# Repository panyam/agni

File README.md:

# Agni

Agni checks schematics and boards for design mistakes, such as an I2C bus with no pull-up, a power
rail with no decoupling, a USB connector with no ESD protection, or a track narrower than the
board's own rules. It reads KiCad, OrCAD Capture, EDIF, xschem and gEDA schematics, and KiCad,
Allegro, Altium, ODB++ and IPC-2581 boards. Every finding names the net or part it fired on and
locates it on the schematic.

**[Open the demo in your browser](https://panyam.github.io/agni/demo/)** and drop a KiCad or EDIF
design on the page, or open one of the example boards. The engine runs in the page as WebAssembly,
so your design is never uploaded.

## Watch a walkthrough

A 33-second walkthrough on Antmicro's open-source Jetson AGX Thor baseboard. It finds a resistor by
name, and the schematic and the board beside it both go to it. Then a click on a test point on the
board takes the schematic to that point's page. `make demo-video JOURNEY=find-a-part` records it.

https://github.com/user-attachments/assets/b399f9d5-5440-4de5-8c01-5e1742dbefdf

A 92-second walkthrough of what changed between two revisions of the same board, Antmicro's rev
1.1.0 and rev 1.1.3. It steps through one change of each kind, an added, a removed and a changed
part, a new, a deleted and a renamed net, and a net whose connections changed, and each step says
what that kind means. `make demo-video JOURNEY=compare-revisions` records it.

https://github.com/user-attachments/assets/1ff74453-c8a3-4b29-8727-99e301f905f8

A 43-second walkthrough that follows a signal outwards from a part on the same board. It starts at
R361, a pull-up on the I2C connector's data line, and walks one hop through small parts, where it
stops at the 3.3 V rail. One hop wider it crosses the level shifter U80 to the module's 1.8 V side,
and then it asks for the route to the rail. `make demo-video JOURNEY=walk-a-signal` records it.

https://github.com/user-attachments/assets/eb9f4803-4316-4d4b-8de4-8aa52e9484a0

## What does it do

- **Runs ERC/DRC-like structural checks.** They catch missing I2C pull-ups, unprotected
  exposed signals, power rails without decoupling, and boards that fail track-width rules. Findings come out in
  plain language and cite the net or component they fire on.
- **Runs a browser viewer.** `agni open <design>` serves one board and prints its URL; `agni serve` opens a
  tree of them. Either renders the design, runs the checks, and locates each finding on the canvas.
- **Runs in the browser with nothing installed.** The engine also compiles to WebAssembly, so the
  [public demo](https://panyam.github.io/agni/demo/) opens a KiCad or EDIF design you drop on the
  page, checks it, queries it and saves a report, without sending the design anywhere.
- **Walks a review checklist and traces signals.** `agni review` scores a design against a team's
  checklist and saves the page, and `agni trace --from U7.3 --to U12.4` follows a signal through
  the series parts between two pins.
- **Checks against datasheets.** It joins a design against extracted datasheet limits and
  checks, for example, that a rail is inside a part's recommended operating range.
- **Diffs revisions over the IR.** It compares two revisions structurally (components, nets,
  connectivity), not as a text diff of the source files, so it survives reformatting and
  rename churn.
- **Renders to SVG or a WebGL canvas**, drawing either the faithful schematic and board
  geometry or an auto-laid-out netlist graph.
- **Answers datalog queries.** `agni query` asks arbitrary questions of the design fact base.
  The rules are built on the same fact base, and the engine is
  [jaala](https://github.com/panyam/jaala).
- **Reads many formats into one IR.** EDIF netlists and schematics, KiCad schematics and
  boards, IPC-2581, xschem, and gEDA all parse into the same `ir.Design`. Adding a reader is
  one entry in `readers/formats/registry.go`.
- **Serves the same answers to other tools.** The CLI calls a set of services, and `agni serve`
  exposes the same services as Connect rpcs. `--remote` sends `query`, `check`, `trace` and `review`
  to a running server, and [`clients/python`](clients/python) is a typed Python client over the CLI
  or a server.

## Try it in 60 seconds

With nothing installed, the [public demo](https://panyam.github.io/agni/demo/) checks a seed
board or a file you drop on it, in your browser.

To run the CLI, install it one of three ways:

```
go install github.com/panyam/agni/cmd/agni@latest
```

or download the tarball for your platform from the
[latest release](https://github.com/panyam/agni/releases/latest) and put `agni` on your PATH, or
run the container image with no install at all:

```
docker run --rm -v "$PWD":/work -w /work ghcr.io/panyam/agni check <board>.kicad_sch
```

Then check the demo board, which has deliberate design issues:

```
curl -sLO https://raw.githubusercontent.com/panyam/agni/main/demo/showcase.fires.kicad_pro
curl -sLO https://raw.githubusercontent.com/panyam/agni/main/demo/showcase.fires.kicad_sch
agni check showcase.fires.kicad_pro
```

```
findings by rule:
  bulk-cap               2
  decoupling-present     2
  esd-protection         2
  i2c-pull-up            1
  input-protection       1
  reverse-blocking-absent 1
  test-point-coverage    2

first 11:
  [warning] bulk-cap: +3V3 (power rail has no bulk capacitor)
  ...
  [error] i2c-pull-up: /SCL (I2C net has no pull-up resistor to a rail)
  [warning] input-protection: VBUS (connector feeds a power input with no fuse or TVS in the path)
  ...
```

`agni open showcase.fires.kicad_sch` serves the board in the browser viewer and prints its URL. Press
Run checks and click a finding to locate its net on the schematic. A release binary carries the
viewer, and a `go install` build downloads it from its release the first time it needs it.

From a checkout, `make agni` builds the same binary into `bin/`, and `make demo` opens both demo
boards, the clean one and the one with issues. See [demo/README.md](demo/README.md).

Each [GitHub release](https://github.com/panyam/agni/releases) attaches a compose bundle pinned to
it. The bundle runs the `ghcr.io/panyam/agni` image over your own boards:

```
AGNI_DESIGNS=./designs docker compose up -d     # the viewer at http://localhost:8080
docker compose run --rm trial /designs/<board>  # a trial report that holds nothing from the board
```

## How it works

Agni normalizes design formats the way a compiler normalizes languages into one AST, so every
analysis downstream is written once and works on all of them. The protobuf IR is the one contract
in the middle. It is defined in `protos/` and generated into `gen/`. Readers are the only code that
knows a file format, and they produce `ir.Design`. They are `readers/edif/`, `readers/kicad/`,
`readers/ipc2581/`, and the xschem/gEDA readers. Everything else consumes the IR and never looks
at a source file. That includes `core/check/`, `core/diff/`, `core/render/`, the query engine and
the web service.

The same shape repeats at two more contracts. N producers fill a geometry IR and N renderers draw
it. N datasheet extractors fill a parameter IR and the checks read it.

## Philosophy

- **One neutral IR serves every format.** A schematic is a schematic whether it came from KiCad,
  EDIF, or IPC-2581. Normalize each format once, and write every analysis once against the
  IR. Add a reader and every check, diff, render, and query works on the new format; add an
  analysis and it works on every format.
- **Format-neutrality is enforced in CI.** Analyses read the IR, never source
  files, and the IR carries no field a second format could not populate. Architectural
  constraints checked in CI keep the core from accreting format-specific special cases.
- **Silence is never coverage.** A check that cannot evaluate reports "not applicable" or
  flags what it could not model; it never returns a false pass. Findings cite the net,
  component, or datasheet page they come from, and unverified data is marked as such. You can
  always tell "clean" from "not checked".
- **Verify against reality.** Readers and rules are checked against the native tools
  (`kicad-cli` ERC/DRC) and real design exports, not only hand-written fixtures. A feature is
  done when it works on a real file.
- **The core is open, with a clear boundary.** The engine is shareable under Apache-2.0.
  Proprietary formats, house rules, and confidential designs live in a private extension that
  depends on the engine without forking it.
- **Agni is written to be legible to software engineers.** EDA carries decades of domain
  vocabulary. Agni maps that vocabulary to concepts software engineers already know (an IR, a
  linter, a semantic diff, a lockfile), so you can contribute without an EE degree. See
  [the software-analogy map](https://panyam.github.io/agni/reference/analogy/).

## Formats read today

| Format | Extensions | Netlist | Faithful geometry |
| --- | --- | --- | --- |
| EDIF 2.0.0 | `.edn` `.edf` `.edif` (netlist), `.eds` (schematic) | yes | schematic |
| KiCad | `.kicad_sch` `.kicad_pcb` `.kicad_pro` | yes | schematic + board |
| IPC-2581 | `.xml` `.cvg` | yes | board |
| xschem | `.sch` (sniffed) | yes | schematic |
| gEDA gschem and Lepton | `.sch` (sniffed) | yes | schematic |
| Telesis | `.tel` | yes | none |
| OrCAD Capture | `.dsn` | yes | schematic |
| Cadence Allegro | `.brd`, from Allegro 16.6 and 17.2 | yes | board |
| Altium Designer | `.PcbDoc` | yes | board |
| ODB++ | a job directory, `.tgz`, `.zip` | yes | board |

A hierarchical EDIF netlist reads its top cell by default and says which blocks it left out. To
read every block it places, pass `--flatten-hierarchy`, set `flatten_hierarchy: true` in the
design's `design.yaml`, or press **Read every block** in the viewer.

## Documentation

Full documentation lives at [panyam.github.io/agni](https://panyam.github.io/agni/).

- [Getting started](https://panyam.github.io/agni/guide/getting-started/) covers installing,
  a first check, reading the report, and gating CI.
- [User guide](https://panyam.github.io/agni/guide/) covers concepts, the CLI, checks, diff, and
  the query language, for someone new to the tool.
- [Software-analogy map](https://panyam.github.io/agni/reference/analogy/) maps
  hardware ideas onto software ones. If you read code but not schematics, start here.
- [Overview](https://panyam.github.io/agni/overview/) opens the engineering docs on IR and
  ingestion, geometry and rendering, semantic diff, and the format primers.
- [examples/README.md](examples/README.md) lists runnable walkthroughs, one per feature.
- [CONSTRAINTS.md](CONSTRAINTS.md) holds the enforceable architectural rules. Read it before
  proposing changes.
- [SECURITY.md](SECURITY.md) says how to report a vulnerability.
- [Open core](https://panyam.github.io/agni/decisions/open-core/) explains the split between this
  public engine and a private extension that adds proprietary readers and rules without forking
  it.

## Status

Agni reads real exports from every listed format and runs its full analysis over them. It is
young, with bounded format coverage (see each reader's notes), a growing rule catalog, and an
early datasheet extraction pipeline. The architecture is settled and the breadth is still
growing. Issues and readers for new formats are welcome.

## Building

`make build` requires Go 1.26.9 and pnpm (for the web viewer bundle). `make testall` also needs
`buf` 1.61 on your PATH, `python3`, a Chromium for the browser tests, and network access to fetch
the pinned sample corpus. `CONTRIBUTING.md` has the details.

```
pnpm install                      # once: the web workspace (web/, web-shared/, datasheet/web/)
make build                        # web bundle + go build ./...
make install                      # install the agni CLI to $GOBIN
make testall                      # the full gate: vet, lint, gosec, gitleaks, Go, wasm, web, browser and Python tests, docs checks
```

## License

Apache-2.0. See [LICENSE](LICENSE) and [NOTICE](NOTICE).

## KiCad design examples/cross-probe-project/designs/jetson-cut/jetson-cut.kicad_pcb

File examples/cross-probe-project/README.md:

# Cross-probe walk project

`make exercise-cross-probe` walks the cross-probe mission (agni issue 1321) on a board: open the
schematic and the board as two linked views, click a part in one and find it in the other, turn the
board over. The gate walks this project, and the mission's real-board run walks the whole Jetson board in
`examples/jetson-project`.

Mission #1586 grows the same walk. Its first steps turn the board view away from C133, a back-side
capacitor, then click C133 on the schematic. The board view turns over to its back on its own and
shows B.Cu (agni issue 1587). A later step hides In5.Cu and clicks `Net-(Q2-G)` on the Power sheet.
That net runs on In5.Cu, so the board view turns In5.Cu back on. With the board view's Follow side
box cleared, the same clicks change neither. Then Back steps to C133 and Forward to `Net-(Q2-G)` again
(agni issue 1588). Last, a click on GND puts "1 of 2" in the canvas bar, and the next-sheet control
opens the other sheet that draws GND, lit and centred (agni issue 1589). To see it by hand, run `agni
open examples/cross-probe-project/designs/jetson-cut` from the repo root, open the Board tile beside
the canvas, and click C133. Press `[` and `]` to step through what you clicked, and `,` and `.` to
step through the sheets.

`designs/jetson-cut` is a cut of the Antmicro baseboard for Jetson AGX Thor, Copyright (c)
2025-2026 Antmicro, licensed under the Apache License, Version 2.0. `make cut` regenerates it from
the fetched samples corpus with `tools/kicadcut`. It keeps two sheets and the board's copper around
the parts on them, so it stays small enough to commit.

| Sheet | Part | Board side | Angle on the board |
| --- | --- | --- | --- |
| USB Debug, PD | C133, C134 | back | 0 |
| USB Debug, PD | C135 | back | 90 |
| USB Debug, PD | C44 | back | -90 |
| USB Debug, PD | R119, R120, D20, D21 | front | 180 |
| USB Debug, PD | R123, R124 | front | 0 |
| Power | Q5, U61, U6 | back | 90 |
| Power | C261, C34 | back | 0 |
| Power | C30, C38 | back | 180 |
| Power | TP76 | front | 0 |
| Power | Q2 | front | 90 |

The board keeps those nineteen footprints, the 397 track segments and 202 vias on their nets inside
4 mm of them, and the board outline. It drops the copper pours, which reach across the whole board,
and the footprint artwork on the User layers, which agni does not draw.

A cut ends some of the design's nets, and the cut schematic names those for itself, so `make cut`
renames each board net to the name kicad-cli's netlist of the cut gives its pads, as KiCad's Update
PCB from Schematic would. agni reads every part pin onto the net kicad-cli's netlist names, and
every pad onto its pin's net. `TestTheCrossProbeCutJoinsItsSchematicToItsBoard` holds the second.

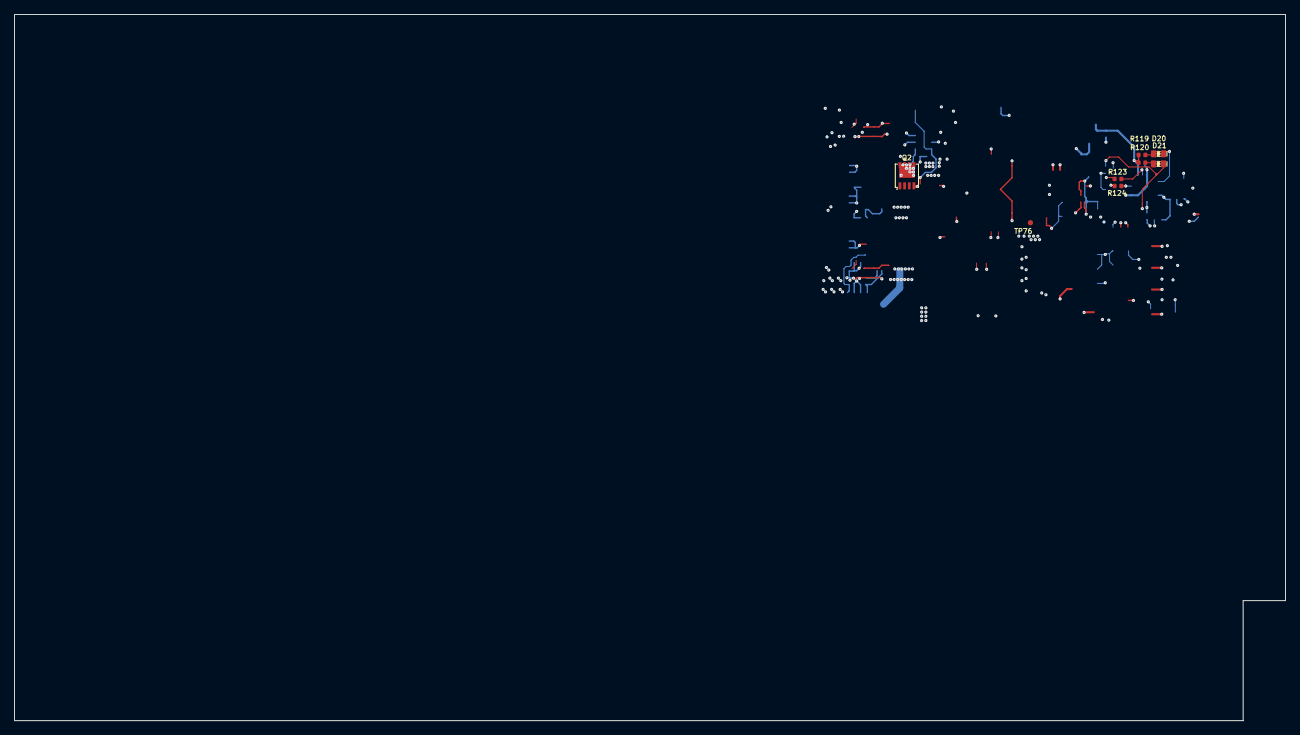
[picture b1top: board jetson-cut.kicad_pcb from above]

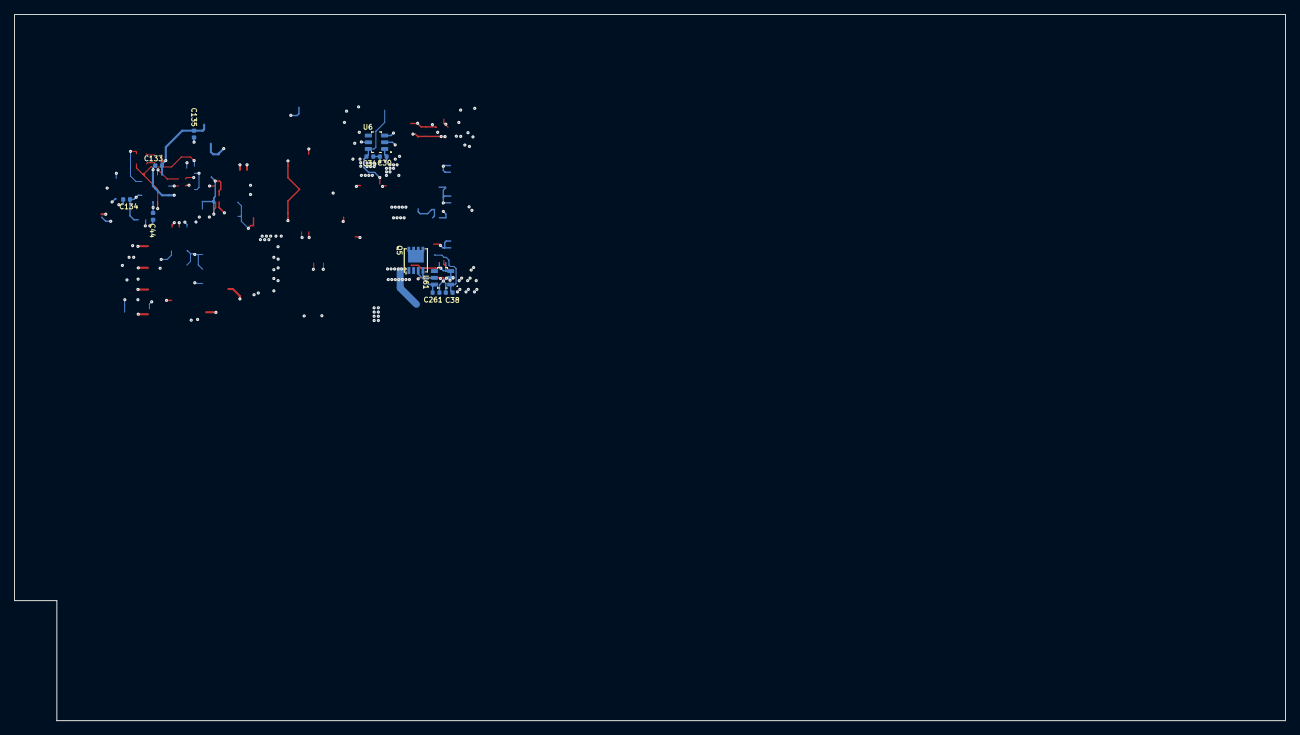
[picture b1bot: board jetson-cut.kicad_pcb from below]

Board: 10 copper layers, 180.0 x 100.0 mm, 19 parts (11 on the bottom side), 9 nets.

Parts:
C30, C38, C44, C133, C134: C_100n_0402; C_0402_1005Metric
C34, C261: C_1u_25V_0402; C_0402_1005Metric
C135: C_10u_0402; C_0402_1005Metric
D20, D21: LED_G_0603_LTST-C190GKT; LED_0603_1608Metric_G
Q2, Q5: SISS05DN-T1-GE3; Vishay_PowerPAK_1212-8_Single
R119, R120: R_200R_0402; R_0402_1005Metric
R123, R124: R_0R_0402; R_0402_1005Metric
TP76: TP_0.75mm_SMD; TP_SMD_0.75mm
U6, U61: LTC4412IS6; SOT-23-6

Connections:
/Power/USBPD1_HV: C38.2, Q5.5 (D), TP76.1, U61.1 (IN)
/USB Debug, PD/FTDI_3V3: C44.1, C133.1, C134.1, C135.2, R119.2, R120.2
GND: C30.1, C34.1, C38.1, C44.2, C133.2, C134.2, C135.1, C261.1, U6.2 (GND), U6.3 (CTL), U61.2 (GND), U61.3 (CTL)
unnamed: D20.2 (A), R119.1
unnamed: D21.2 (A), R120.1
unnamed: C30.2, Q2.5 (D), U6.1 (IN)
unnamed: Q2.4 (G), U6.5 (GATE)
unnamed: Q5.4 (G), U61.5 (GATE)
unnamed: C34.2, C261.2, Q2.1 (S), Q2.2 (S), Q2.3 (S), Q5.1 (S), Q5.2 (S), Q5.3 (S), U6.6 (SENSE), U61.6 (SENSE)

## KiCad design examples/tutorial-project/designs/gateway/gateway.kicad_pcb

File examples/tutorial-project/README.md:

# Tutorial project

The worked example the tutorial track is built on: one synthetic board and the project files a team
wraps around it. Every part, MPN, vendor, and datasheet value here is invented, so the whole folder
is redistributable and nothing on it is anyone's real design.

## Try it

```
make review
```

That runs the `review` checklist in `project.yaml` over the bundled board with every tier this
project supplies, and prints one outcome per item. `make help` lists the rest.

Note what the command does **not** carry: no `--conventions`, no `--profile-path`, no `--params`, no
`--intent-path`. The board resolves to this project, and the project's config is read from
`project.yaml` and from beside it. That is also what keeps it from reaching anywhere else. A design in another project,
or in none, cannot be checked against these rules, because config travels along the design-to-project
edge rather than along the command line.

## Layout

This is the shape a real review project takes. Two kinds of file live here.

**Per-project**, shared by every design:

| Path | What it is |
|---|---|
| `project.yaml` | the project's name, which is what makes this folder a project rather than a folder |
| `project.yaml` `conventions:` | house naming, which says which net names are rails and what a legal name looks like |
| `project.yaml` `checklists.review` | the checklist of questions this team asks of every board, and the project's default since it is written first |
| `project.yaml` `checklists.house` | a second checklist whose inline query calls this project's own library in `lib/`, run with `--checklist house` |
| `profiles/` | interface declarations, one per bus this team designs with |
| `params/` | datasheet parameter sets, one per part worth checking against its limits |
| `lib/` | this team's own derived relations, one Datalog module per `.dl` file, such as `house.pmic_rail` |
| `reports/<design>/` | the outcome of a run on one design, written by `make report` |

**Per-design**, one set per folder under `designs/`:

| Path | What it is |
|---|---|
| `design.yaml` | the design's name, which file is its entry, and which files are views of it |
| `gateway.edn` | the netlist, `gateway-rev-b.edn` a later revision of it, and `gateway-rev-c.edn` one more that renames and rewires a net, for `diff --rename-approx` |
| `gateway.kicad_sch` | the same board as a KiCad schematic, with `symbols/` as an external library |
| `gateway.kicad_pcb` | the same board's copper, for the board-tier checks |
| `design.yaml` `intent:` | what this board is supposed to be: declared modules and what each rail is |

Intent is per-design because each board has its own intended architecture. Conventions, profiles,
and parameters are per-project because they describe the team, not the board.

The two descriptors are what let you name a **design** instead of a file. `agni check
designs/gateway` reads the entry `design.yaml` declares and picks up the board companion for the
copper checks, so the connectivity rules and the board rules run from one argument. Naming a
declared companion (`agni check designs/gateway/gateway.kicad_pcb`) reads the entry instead and says
so on stderr, because a board export is a view of the design rather than a second source of it. Pass
`--as-named` when reading a view as a netlist is the point, which is what `make check-views` does.

## What the board is built to show

The board is deliberately imperfect. Each flaw exists so some part of the tool has something true
to report rather than a contrived one.

- **Rails are named function-first** (`PMIC_CORE_3V3`), which the built-in rail vocabulary does not
  match. Without the `conventions:` section the only rail on the board is `GND`. That is what the
  lexicon half of a conventions section is for, and running `agni check` with and without it shows
  the difference.
- **CAN is present, complete, and terminated, but has no ESD part on the pair.** So the built-in
  CAN profile has exactly one real finding. `profiles/can.yaml` then supersedes that built-in and
  adds a standby signal this project always routes, which the board does not, so a second finding
  appears when the overlay profile loads.
- **LIN is absent entirely.** Its checklist item must not score a pass just because a check for a
  bus that is not there found nothing to complain about.
- **U2's datasheet parameters are a mock placeholder**, not a transcription. Its finding reports as
  `provisional` rather than `fail`, which is the engine declining to call a defect on data nobody
  has checked. `params/acme-buck-3v3.textproto` is the seeded-and-trusted contrast.
- **One intent declaration is deliberately wrong.** The core domain is declared at 3.3 V while its
  rail is an actual 1.8 V rail, so the intent check has a real deviation to find.
- **The entry file is a netlist, which carries no copper.** The board-tier item is answered from
  the `.kicad_pcb` that `design.yaml` declares as a companion. A design declaring no board reads
  `n/a` there, which means the question does not apply to what was loaded, and that is not a pass.

## A note on the netlist

One rule about the EDIF decides whether pins connect at all, and it is easy to get wrong when
writing one by hand.

A `portRef` names a port by its **designator**, not by the port's name. Use the name and the
connection never joins to the pin, so pin-level rules see an unconnected part while `stats` looks
perfectly healthy.

Each part cell here also declares its own `(designator "<prefix>")`, which is how a cell states the
reference-designator prefix its instances use. That is good practice rather than a requirement,
since a cell that omits it falls back to the prefix on each instance's own ref-des. It used to be
required here for a different reason, because the reader would take a *port's* designator when a cell
declared none, and every component of that cell then classified as unknown. That was agni issue 109
and it is fixed.

## What this fixture is, and how its views stay in step

`examples/tutorial-project/` is the shareable review-project fixture the docsite tutorial runs on, a
synthetic sample board in three views (`.edn` plus a rev-b, a `.kicad_sch` with an external symbol
library, a `.kicad_pcb`) with a `project.yaml` carrying its conventions and checklists,
`profiles/`, `params/`, and a
`design.yaml` per design carrying its `intent:` section. The KiCad views are GENERATED from the netlist by `tools/`. From
inside `examples/tutorial-project/`, `make check-views` fails if the three stop describing the same
design, and `make regen-views` rebuilds them after any netlist edit (both targets live in this
folder's own Makefile, not the root one). It is not a Go module, so `make testall`'s
`examples/*/go.mod` glob skips it.

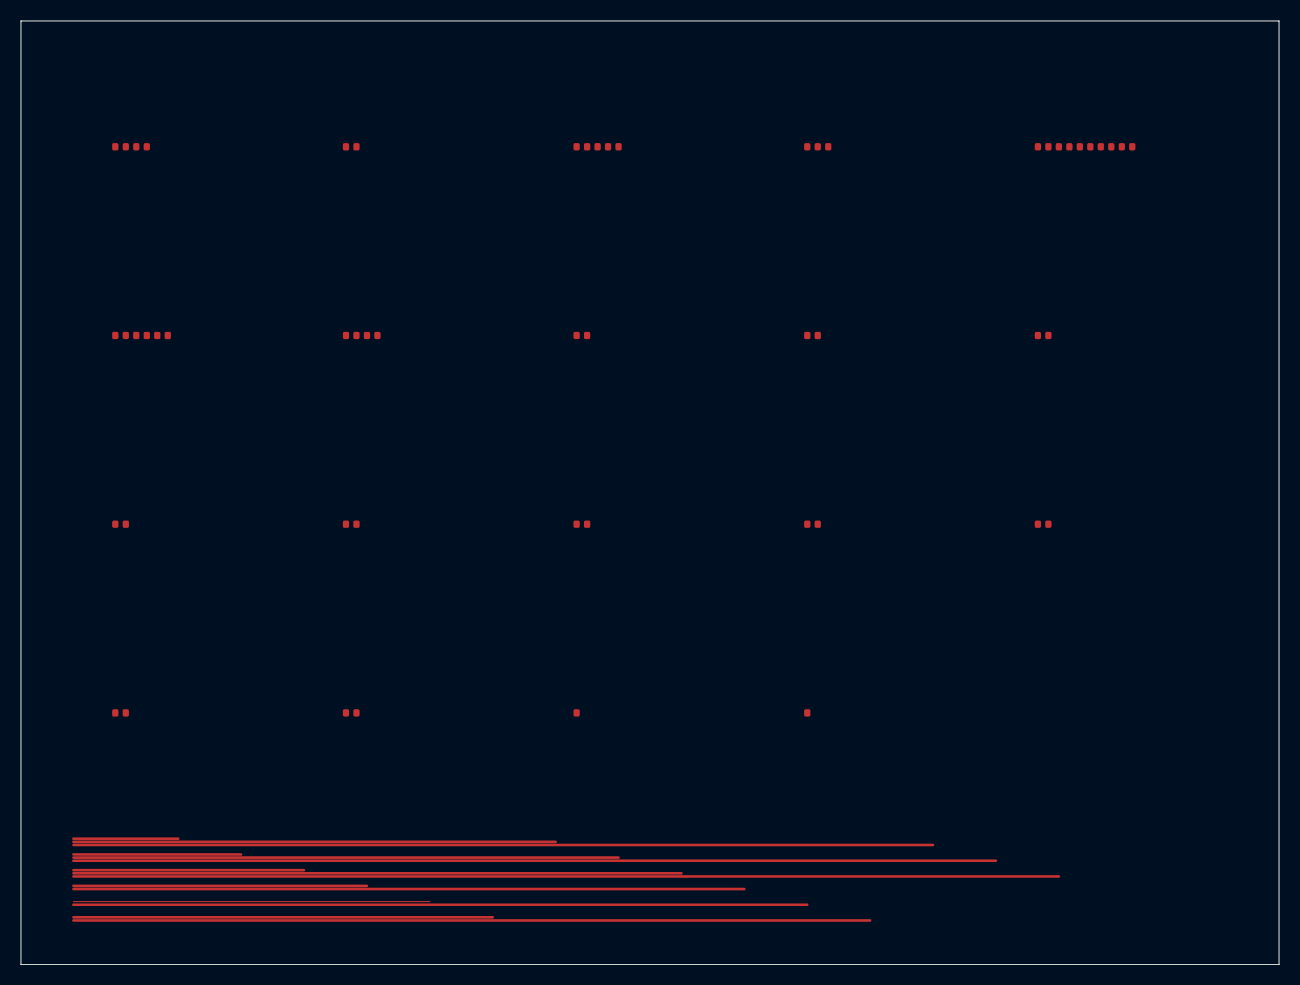
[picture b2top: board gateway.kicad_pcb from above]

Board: 2 copper layers, 120.0 x 90.0 mm, 19 parts (0 on the bottom side), 15 nets.

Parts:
C1: 22uF; C_0402
C2, C4: 100nF; C_0402
C3: 10uF; C_0402
C5, C6: 18pF; C_0402
D1: TVS; D_SOD-323
J1: CONN4; J_1x04
R1: 120; R_0402
R2, R3: 10k; R_0402
TP1, TP2: TESTPOINT; TestPoint_Pad_D1.0mm
U1: BUCK; SOIC-8_3.9x4.9mm_P1.27mm
U2: LDO; SOIC-8_3.9x4.9mm_P1.27mm
U3: MCU; SOIC-8_3.9x4.9mm_P1.27mm
U4: CANXCVR; SOIC-8_3.9x4.9mm_P1.27mm
U5: EEPROM; SOIC-8_3.9x4.9mm_P1.27mm
Y1: XTAL; Crystal_SMD_3225

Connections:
CAN1_CANH: J1.3, R1.1, U4.5
CAN1_CANL: J1.4, R1.2, U4.6
CAN1_RXD: U3.7, U4.4
CAN1_TXD: U3.6, U4.3
GND: C1.2, C2.2, C3.2, C4.2, C5.2, C6.2, D1.2, J1.2, U1.3, U2.3, U3.3, U4.2, U5.2
I2C_SCL: U3.8, U5.3
I2C_SDA: U3.9, U5.4
MCU_NRST: R3.1, U3.10
PMIC_CORE_3V3: C1.1, C2.1, TP1.1, U1.2, U2.1, U3.2, U4.1, U5.1
PMIC_EN: R2.1, U1.4
PMIC_IO_1V8: C3.1, C4.1, TP2.1, U2.2, U3.1
PMIC_MAIN_12V0: D1.1, J1.1, R2.2, U1.1
PMIC_PG: R3.2, U1.5
XTAL_IN: C5.1, U3.4, Y1.1
XTAL_OUT: C6.1, U3.5, Y1.2

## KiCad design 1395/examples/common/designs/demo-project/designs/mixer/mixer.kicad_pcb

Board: 0 copper layers, 3 parts (0 on the bottom side), 3 nets, no tracks yet.

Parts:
R1, R2: 10k; R_0603
U1: OPAMP; SOIC-8

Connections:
GND: R2.2, U1.4
SIG: R1.2, R2.1, U1.2
VCC: R1.1, U1.1
